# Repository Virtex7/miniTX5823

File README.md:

# miniTX5823
The miniTX5823 is a video and audio transmitter module designed for fpv. The Software ist compatible to [tx5823-pro](https://github.com/sheaivey/tx5823-pro).

## Hardware
The module contains the popular TX5823 video transmitter, modded so that channel selction via SPI ist possible. In addition there is a 5V buckconverter on the board with up to 2A output current, allowing 3s and 4s input. For clean voltage the TX5823 has its own, ultra low noise linear regulator.

Above all there is a IR transistor and a button on the module which makes easy binding with your receiver possible. You select the channel at your receiver in manual mode an bring it next to your transmitter. By pushing the button the transmitter changes to the channel of the receiver. The [rx5808-pro-diversity](https://github.com/sheaivey/rx5808-pro-diversity/) or other compatible receivers have the necessary IR diode to use this feature.

Dimensions of the PCB are 4cm x 3cm

## Software
For the beginning the board will run [tx5823-pro](https://github.com/sheaivey/tx5823-pro).
For future it is planned to add support for the onboard WS2812B RGB led

## Other similar hardware/projects
* [TX5823 by ep092](https://github.com/ep092/TX5823)
* [RX5808 by Virtex7](https://github.com/Virtex7/RX5808)
* [tx5823-pro by sheaivey](https://github.com/sheaivey/tx5823-pro)
* [rx5808-pro-diversity by sheaivey](https://github.com/sheaivey/rx5808-pro-diversity/)

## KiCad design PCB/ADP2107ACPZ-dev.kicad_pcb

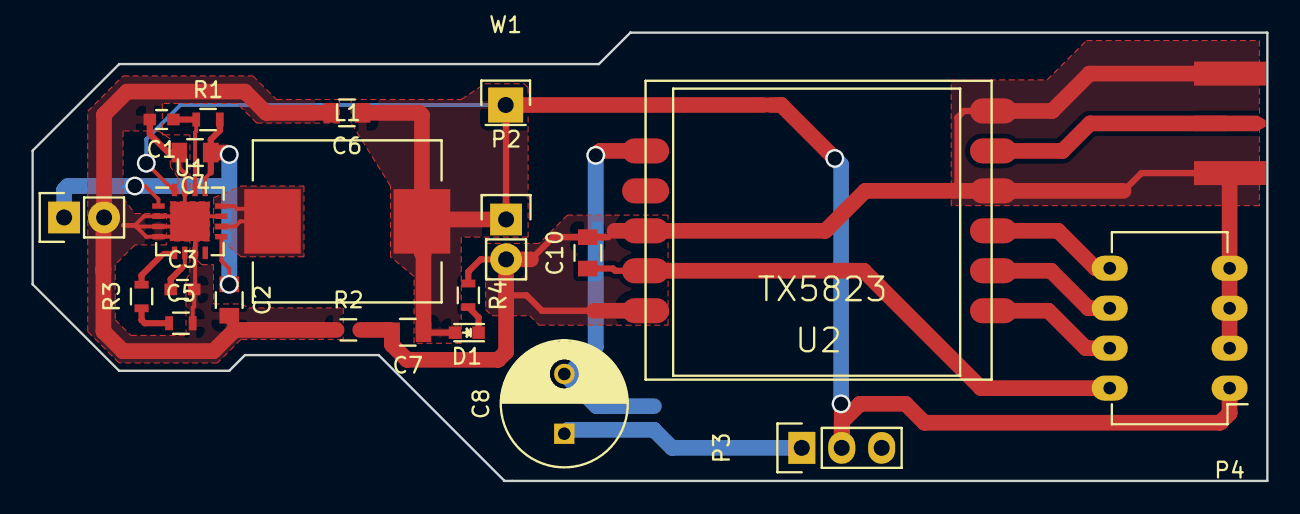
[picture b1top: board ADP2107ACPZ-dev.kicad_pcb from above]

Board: 2 copper layers, 78.5 x 28.5 mm, 24 parts (1 on the bottom side), 17 nets.

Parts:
C1, C9: 100n; C_0603
C2, C4, C6, C10: 10u; C_0805
C3: 1n; C_0603
C5: 1n; R_0603
C7: 4,7u; C_0805
C8: 470u; C_Radial_D8_L13_P3.8
D1: green; LED_0603
L1: 3,3u; Neosid_Inductor_SM-PIC1004H
P1, P2: CONN_01X02; Pin_Header_Straight_1x02
P3: CONN_01X03; Pin_Header_Straight_1x03
P4: CONN_02X04; DIP-8_W7.62mm_LongPads
R1: 10; R_0603
R2: 0; R_0603
R3: 68k; R_0603
R4: 1k; R_0603
SMA_E1: SMA_EDGE
U1: ADP2107; QFN-16-1EP_4x4mm_Pitch0.65mm
U2: TX5823
W1: TEST_1P; Pin_Header_Straight_1x01

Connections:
+3.3VP: C6.1, C7.1, D1.2, L1.2, P2.1, P3.2, P4.1, U1.16, W1.1
+5V: C2.1, C4.1, P1.1, R1.2, U1.1, U1.9, U1.13
GND: C7.2, C10.2, P2.2, P3.3, P4.3, P4.5, P4.7, R2.2, R4.1, SMA_E1.0, SMA_E1.2, U2.3, U2.5, U2.9, U2.11
GNDPWR: C1.2, C2.2, C3.2, C4.2, C5.2, C6.2, P1.2, R2.1, U1.2, U1.3, U1.4, U1.7, U1.11, U1.15, U1.17
unnamed: C1.1, R1.1, U1.14
unnamed: C3.1, U1.6
unnamed: C5.1, R3.1
unnamed: C8.1, C9.2, P3.1
unnamed: C8.2, C9.1, U2.1
unnamed: C10.1, P4.2, U2.4
unnamed: D1.1, R4.2
unnamed: L1.1, U1.10, U1.12
unnamed: P4.4, U2.6
unnamed: P4.6, U2.7
unnamed: P4.8, U2.8
unnamed: R3.2, U1.5
unnamed: SMA_E1.1, U2.10

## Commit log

2016-02-17 initial commit - dev layout fertig.
2016-02-18 Datenblätter der Sende- und Verstärkerchips dazugefügt
2016-03-17 dateien verschoben, damit Platz für neues ist!
2016-03-21 initialer commit von Schaltplan und Layout. noch unfertig.
2016-03-26 bild hinzugefügt
2016-03-26 added pictures
2016-03-26 added picture in README
2016-03-26 added similar hardware section
2016-03-26 fixed error in list
2016-03-26 finalised shematic and pcb
